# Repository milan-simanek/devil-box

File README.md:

# devil-box
A box with a little devil inside

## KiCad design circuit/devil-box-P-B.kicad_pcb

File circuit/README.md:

Alternatives
============

- devil-box-N = Arduino power controlled by N-MOSFET on ground side.

- devil-box-P = Arduino power controlled by P-MOSFET on Vcc side.

Revisions
=========

Revision A

  - initial revision, home-made motion sensor

Revision B

  - PCB developed
  - SW-520D sensor

Revision C

  - never implemented, future changes

Changes:
========

N-A -> N-C

- add R6 10k - Arduino can detect unexpected box motion
- better component placement in schematics
- motion sensor changed to SW-520D
- rezistors R1-R4 changed to 10k

P-B -> P->C

- add R6 10k - Arduino can detect unexpected box motion
- better component placement in schematics
- change A7->A0 (A7 is analog in put only)
- change T4: IRF9Z34N
- improve power supply for Arduino by schottky D1
  (internal linear power regulater has voltage drop 1.2V [datasheet max 2V])
- add C3 to limit interference voltage spikes

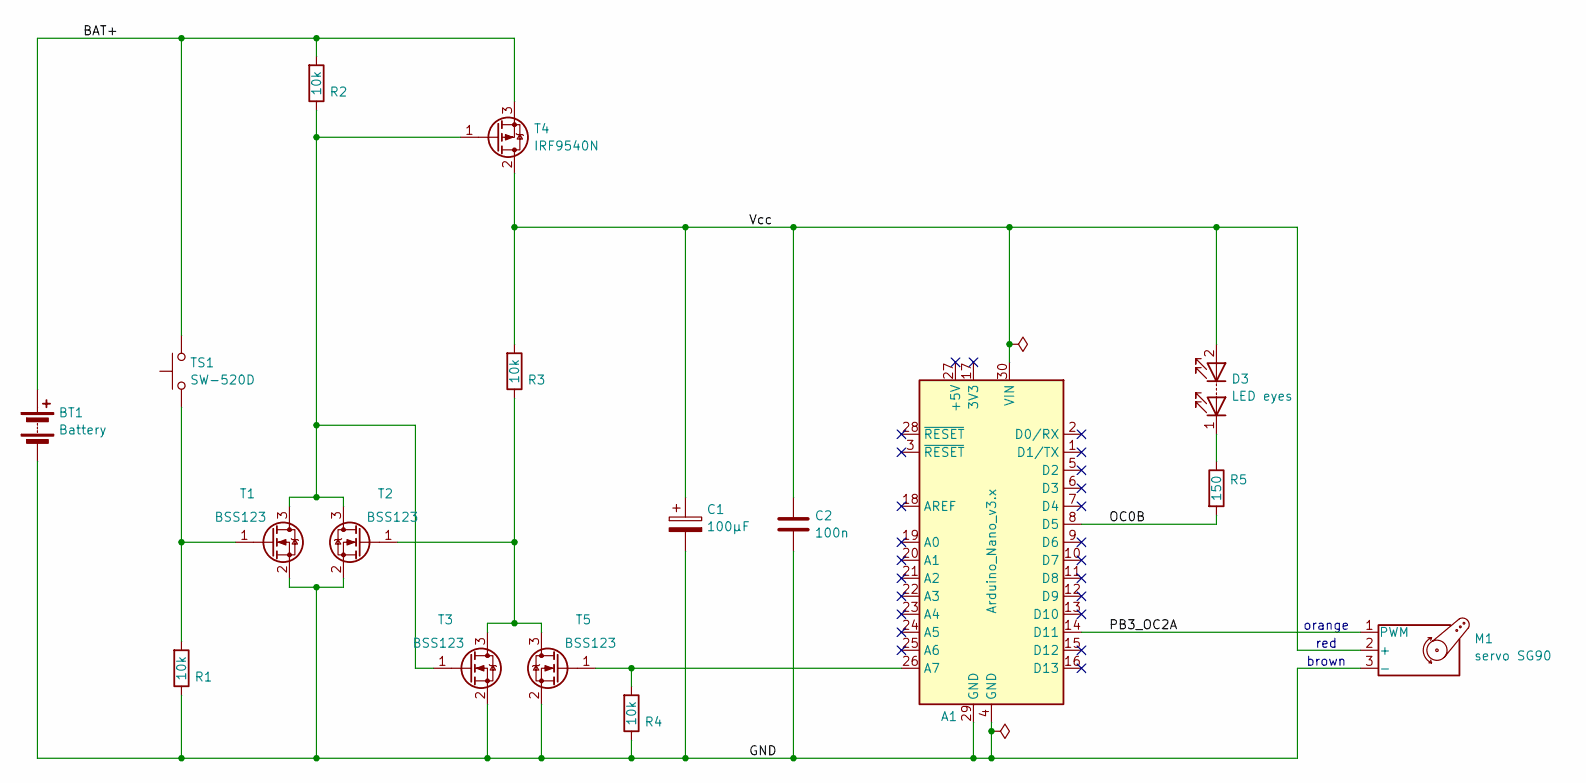
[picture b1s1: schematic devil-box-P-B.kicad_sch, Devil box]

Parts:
A1: Arduino_Nano_v3.x; Arduino_Nano_WithMountingHoles
BT1: Battery; PinHeader_1x02_P2.54mm_Vertical
C1: 100μF; CP_Radial_D5.0mm_P2.50mm
C2: 100n; C_Disc_D5.0mm_W2.5mm_P5.00mm
D3: LED eyes; PinHeader_1x02_P2.54mm_Vertical
M1: servo SG90; PinHeader_1x03_P2.54mm_Vertical
R1, R2, R3, R4: 10k; R_0402_1005Metric; LCSC C25744
R5: 150; R_0805_2012Metric; LCSC C17471
T1, T2, T3, T5: BSS123; SOT-23; LCSC C79015
T4: IRF9540N; TO-220-3_Horizontal_TabDown
TS1: SW-520D; CP_Radial_D6.3mm_P2.50mm

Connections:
/BAT+: BT1.1 (+), R2.2, T4.3 (S), TS1.1
/GND: A1.4 (GND), A1.29 (GND), BT1.2 (-), C1.2, C2.2, M1.3 (-), R1.1, R4.1, T1.2 (S), T2.2 (S), T3.2 (S), T5.2 (S)
/OC0B: A1.8 (D5), R5.2
/PB3_OC2A: A1.14 (D11), M1.1 (PWM)
/Vcc: A1.30 (VIN), C1.1, C2.1, D3.2 (A), M1.2 (+), R3.2, T4.2 (D)
unnamed: A1.26 (A7), R4.2, T5.1 (G)
unnamed: D3.1 (K), R5.1
unnamed: R2.1, T1.3 (D), T2.3 (D), T3.1 (G), T4.1 (G)
unnamed: R1.2, T1.1 (G), TS1.2
unnamed: R3.1, T2.1 (G), T3.3 (D), T5.3 (D)

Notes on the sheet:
orange
brown
red

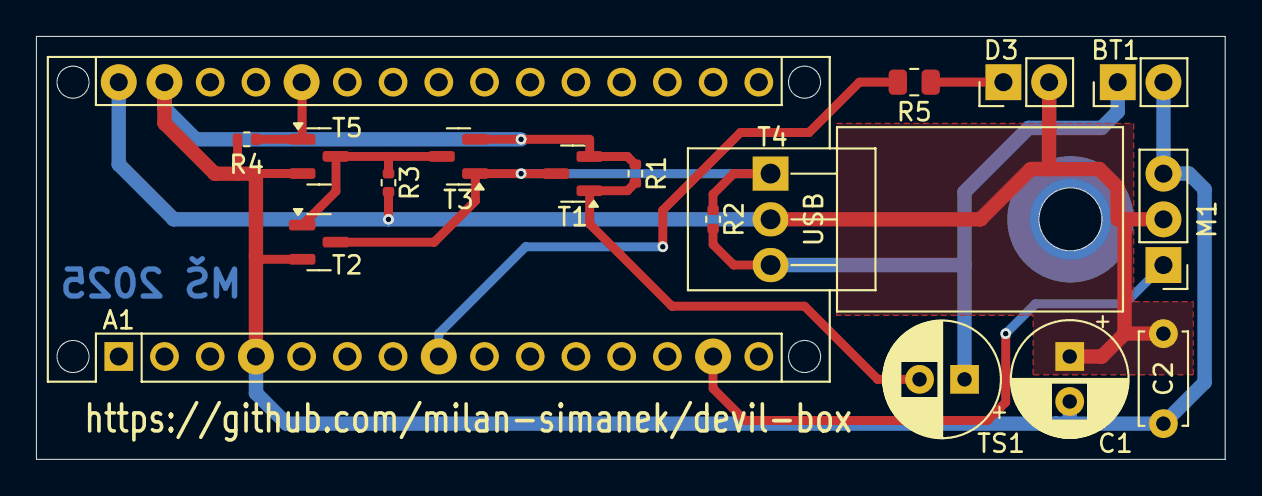
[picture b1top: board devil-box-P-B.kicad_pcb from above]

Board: 2 copper layers, 66.0 x 23.5 mm, 17 parts (0 on the bottom side), 10 nets.

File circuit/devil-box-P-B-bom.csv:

"Comment","Designator","Footprint","LCSC Part Number"
"10k","R1,R2,R3,R4","0402","C25744"
"150R","R5","0805","C17471"
"BSS123","T1,T2,T3,T5","SOT-23","C79015"

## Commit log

2024-08-30 add schematics
2025-03-07 add capacitor; changed stop pin D4-A0
2025-03-07 footprints assigned, LED series for better implementation
2025-03-07 complementar option added
2025-03-07 main MOSFET changed
2025-03-07 PCB created for P variant
2025-03-07 new PCB designed (smaller+using position sensor)
2025-03-11 revA uses external motion sensor
2025-03-11 add rev C
2025-03-11 add .gitignore
2025-03-11 add servo wire labels
2025-03-13 change P-MOSFET to IRF9Z34N, add color labels to servo wires
2025-03-13 gitignore updated
2025-03-13 add C3, D1
2025-03-18 the first arduino implementation
2025-03-20 arduino development
2026-03-19 upgrade to KiCAD 9
